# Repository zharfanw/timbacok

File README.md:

# TIMBACOK
TIMBACOK merupakan mobil listrik Formula Student ala COLEKMES.COM. Jadi gini, repo ini memang berisi tentang hal teknis secara elektrik tentang TIMBACOK. Namun tentang teruji atau hal-hal lainnya, kami tidak bertanggung jawab dan tentu itu resiko anda sendiri.

## Pembaharuan terakhir

 - 18 Nov 2019 : Menambahkan Rangkaian Shutdown Circuit

<!--stackedit_data:
eyJoaXN0b3J5IjpbLTExNjQwNzczMTQsLTM4NjAwNTQ3XX0=
-->

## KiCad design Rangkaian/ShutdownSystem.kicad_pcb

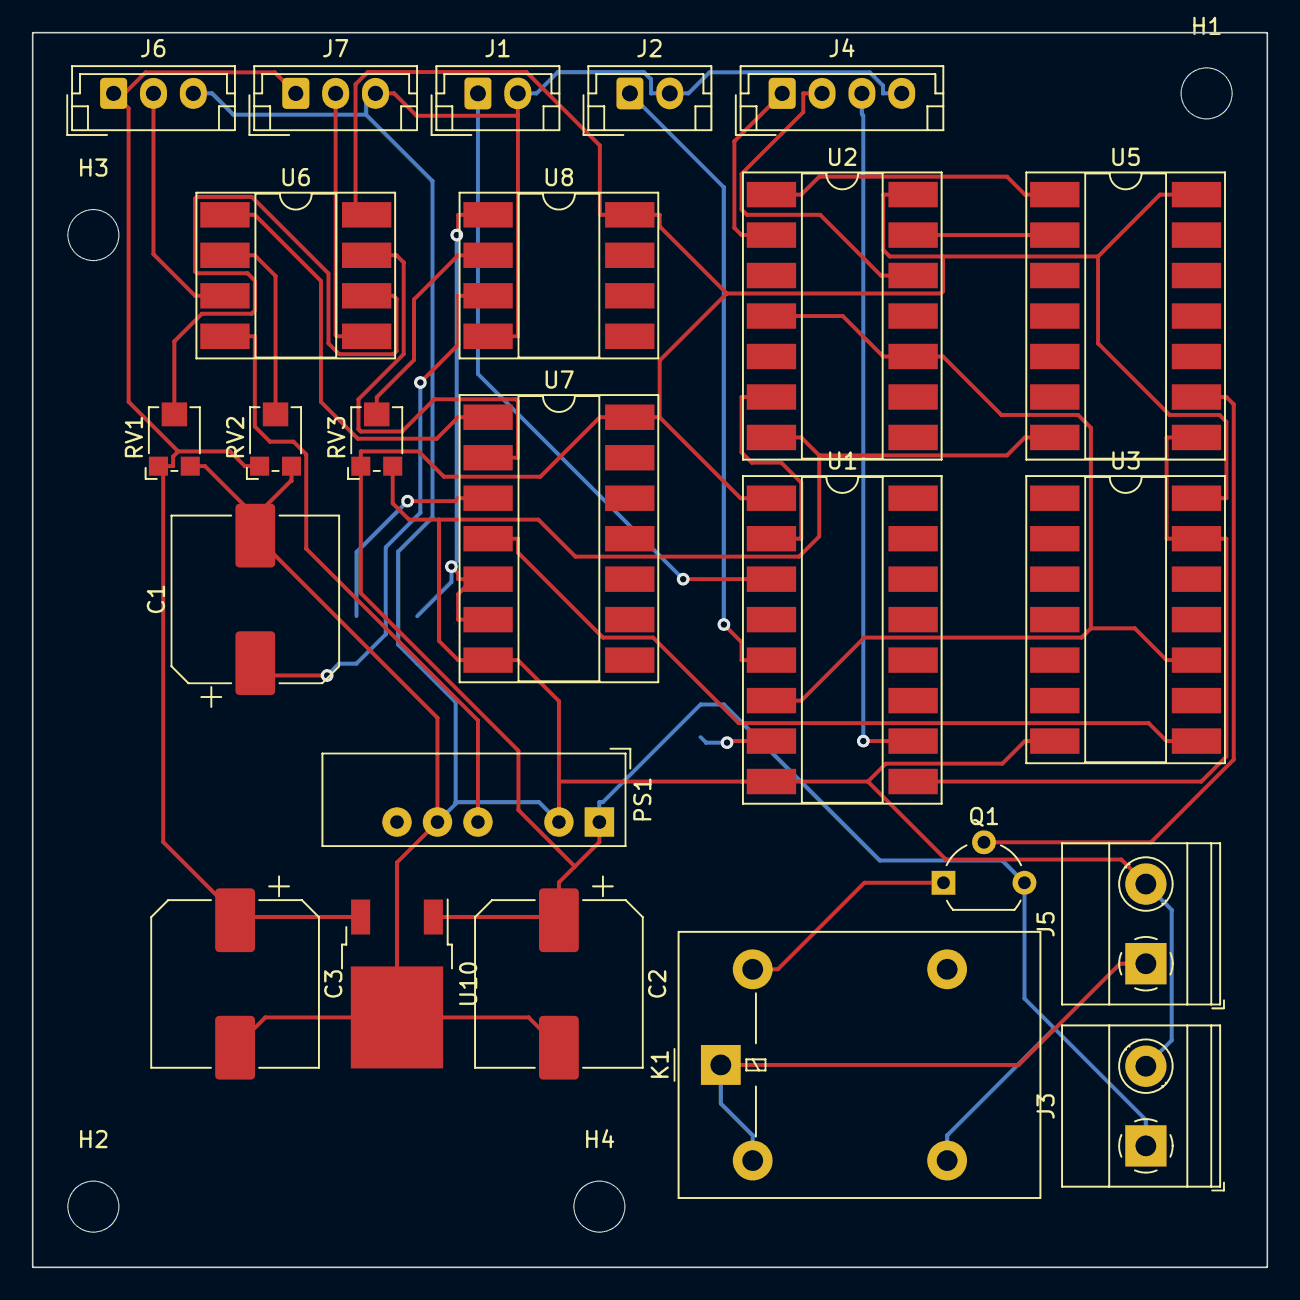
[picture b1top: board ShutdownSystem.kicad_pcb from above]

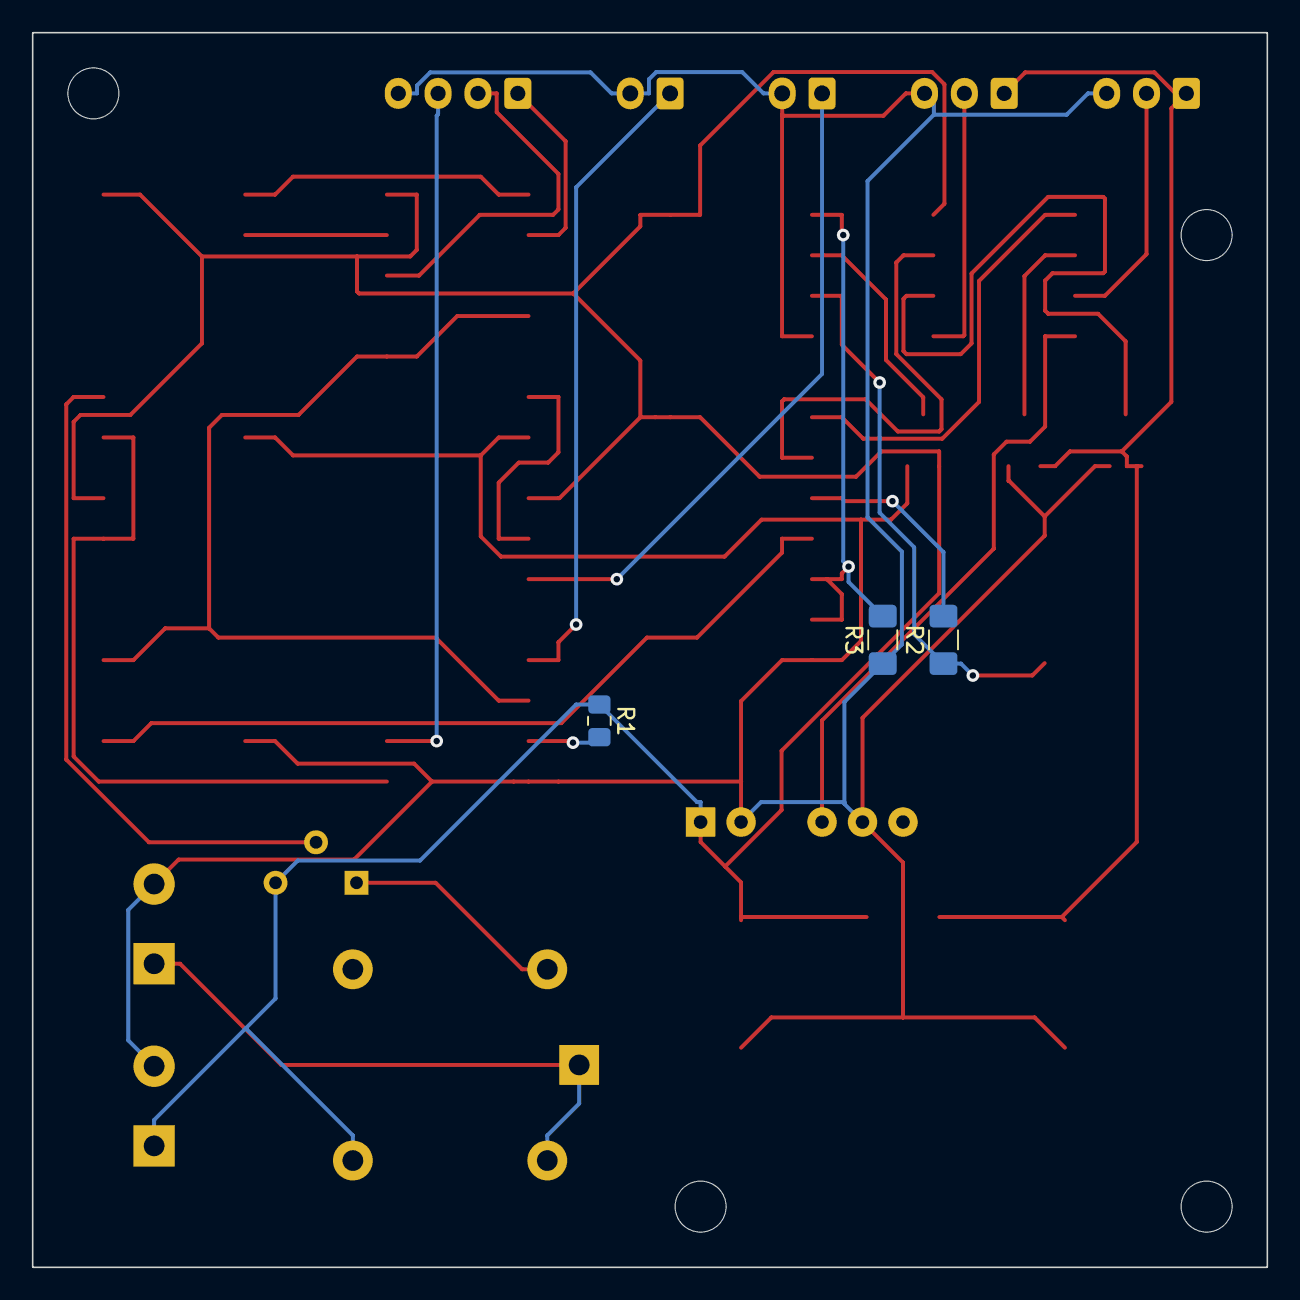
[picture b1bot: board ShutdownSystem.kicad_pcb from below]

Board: 2 copper layers, 77.5 x 77.5 mm, 31 parts (3 on the bottom side), 29 nets.

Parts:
C1: CP; CP_Elec_10x10
C2, C3: 470uF; CP_Elec_10x10
H1, H2, H3, H4: MountingHole; MountingHole_3.2mm_M3
J1, J2: Conn_01x02_Female; JST_EH_B2B-EH-A_1x02_P2.50mm_Vertical
J3, J5: ShutdownCircuitCon; TerminalBlock_Phoenix_MKDS-1,5-2_1x02_P5.00mm_Horizontal
J4: IndicatorCon; JST_EH_B4B-EH-A_1x04_P2.50mm_Vertical
J6: CurrentCon; JST_EH_B3B-EH-A_1x03_P2.50mm_Vertical
J7: BrakeCon; JST_EH_B3B-EH-A_1x03_P2.50mm_Vertical
K1: FINDER-40.11; Relay_SPDT_Omron-G5LE-1
PS1: IA1212S; Converter_DCDC_XP_POWER-IAxxxxS_THT
Q1: 2N2219; TO-92L_Wide
R1: R; R_0805_2012Metric_Pad1.15x1.40mm_HandSolder
R2, R3: R; R_1206_3216Metric_Pad1.42x1.75mm_HandSolder
RV1, RV2, RV3: R_POT; Potentiometer_Bourns_TC33X_Vertical
U1: 4049; DIP-16_W8.89mm_SMDSocket_LongPads
U2, U3: 4013; DIP-14_W8.89mm_SMDSocket_LongPads
U5: 4025; DIP-14_W8.89mm_SMDSocket_LongPads
U6, U8: LM2904; DIP-8_W8.89mm_SMDSocket_LongPads
U7: 4081; DIP-14_W8.89mm_SMDSocket_LongPads
U10: L7805; TO-252-2

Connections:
+5V: C3.1, J6.1, J7.1, RV1.1, RV2.1, U10.3
+VDC: C2.1, J3.1, K1.3, PS1.1, Q1.3, R1.1, RV3.1, U1.1, U2.14, U3.14, U5.14, U6.8, U7.14, U8.8, U10.1
-VDC: PS1.4, U6.4
/AMSIndicator: J4.2, U2.12
/AMSStatus: J2.1, U1.5
/BSPDCircuit/BSPDStatus: U3.8, U7.4
/BSPDCircuit/BrakeSignal: J7.2, U6.5
/BSPDCircuit/CurrentSignal: J6.2, U6.3
/BSPDIndicator: J4.3, U1.10
/IMDIndicator: J4.1, U2.2
/IMDStatus: J1.1, U1.3
/Reset: R1.2, U1.7
GND: C1.2, C2.2, C3.2, J1.2, J2.2, J3.2, J4.4, J5.2, J6.3, J7.3, PS1.2, PS1.5, R3.1, RV1.3, RV2.3, RV3.3, U1.8, U2.7, U3.7, U5.7, U7.7, U8.4, U10.2
unnamed: C1.1, R2.1, U8.3
unnamed: J5.1, K1.1, K1.2
unnamed: K1.5, Q1.1
unnamed: Q1.2, U5.9
unnamed: R2.2, U7.3
unnamed: R3.2, U7.5, U7.6, U8.1
unnamed: RV1.2, U6.6
unnamed: RV2.2, U6.2
unnamed: RV3.2, U8.2
unnamed: U1.2, U2.6
unnamed: U1.6, U2.4, U2.10, U3.10
unnamed: U1.9, U3.13, U5.8
unnamed: U2.1, U5.1
unnamed: U2.13, U5.2
unnamed: U6.1, U7.1
unnamed: U6.7, U7.2

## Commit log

2019-11-19 README.md updated from https://stackedit.io/
2019-11-19 Menambahkan rangkaian Shutdown
